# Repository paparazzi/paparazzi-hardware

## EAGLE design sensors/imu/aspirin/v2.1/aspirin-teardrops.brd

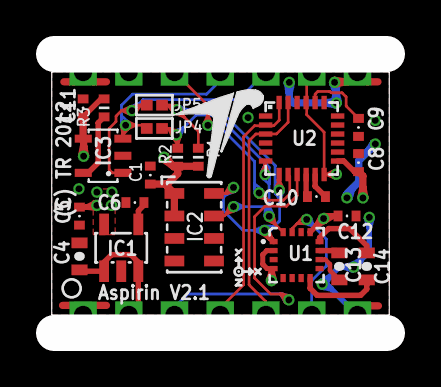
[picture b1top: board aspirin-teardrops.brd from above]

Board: 4 copper layers, 18.8 x 15.5 mm, 23 parts (0 on the bottom side), 20 nets.

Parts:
ASP1: ASPIRIN; ASPIRIN_CASTELLATED
C1, C8, C10, C11, C12: 100n; 0402-CAP
C4: 2.2uF/Low ESR; 0603-CAP
C5: 4.7uF/10V/Low ESR; 0402-CAP
C6: 10nF; 0402-CAP
C9: 2n2; 0402-CAP
C13: 4.7uF/10V/Low ESR; 0603-CAP
C14: 220n/Low ESR; 0603-CAP
IC1: LP2992; SOT23-5
IC2: MS5611; QFN-MS5611
IC3: >4KBIT SERIAL EEPROM HALF PROTECT; SOT23-5
JP4, JP5: 0/DNP; 0402-SQJMP
R1, R2, R3: 4k7; 0402-RES
U1: HMC5883; PLCC16-HMC5883
U2: MPU-6000; QFN24-NO-PAD
U$1: TR-LOGO

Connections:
+3V3: C1.P$1, C5.P$1, C8.P$1, C11.P$1, C12.P$1, IC1.5, IC2.1, IC2.2, IC3.4, R1.P$1, R2.P$1, R3.P$2, U1.2, U1.4, U1.13, U2.13
+6V5: ASP1.2, C4.P$1, IC1.1, IC1.3
ACC_CS: ASP1.12, U2.8
GND: ASP1.1, ASP1.7, ASP1.8, ASP1.14, C1.P$2, C4.P$2, C5.P$2, C6.P$1, C8.P$2, C9.P$2, C10.P$2, C11.P$2, C12.P$2, C13.P$2, IC1.2, IC2.3, IC2.4, IC2.5, IC3.2, U1.9, U1.11, U2.1, U2.11, U2.18
GYRO_INT: ASP1.9, U2.12
MAG_INT: ASP1.6, U1.15
MISO: ASP1.3, U2.9
MOSI: ASP1.4, U2.24
unnamed: C9.P$1, U2.20
unnamed: C10.P$1, U2.10
unnamed: C13.P$1, U1.10
unnamed: IC3.5, R3.P$1
unnamed: C6.P$2, IC1.4
unnamed: C14.P$2, U1.8
unnamed: C14.P$1, U1.12
SCK: ASP1.5, U2.23
SCL: IC2.8, JP5.P$2, R1.P$2, U1.1, U2.7
SDA: IC2.7, JP4.P$2, R2.P$2, U1.16, U2.6
XSCL: ASP1.10, IC3.1, JP5.P$1
XSDA: ASP1.11, IC3.3, JP4.P$1

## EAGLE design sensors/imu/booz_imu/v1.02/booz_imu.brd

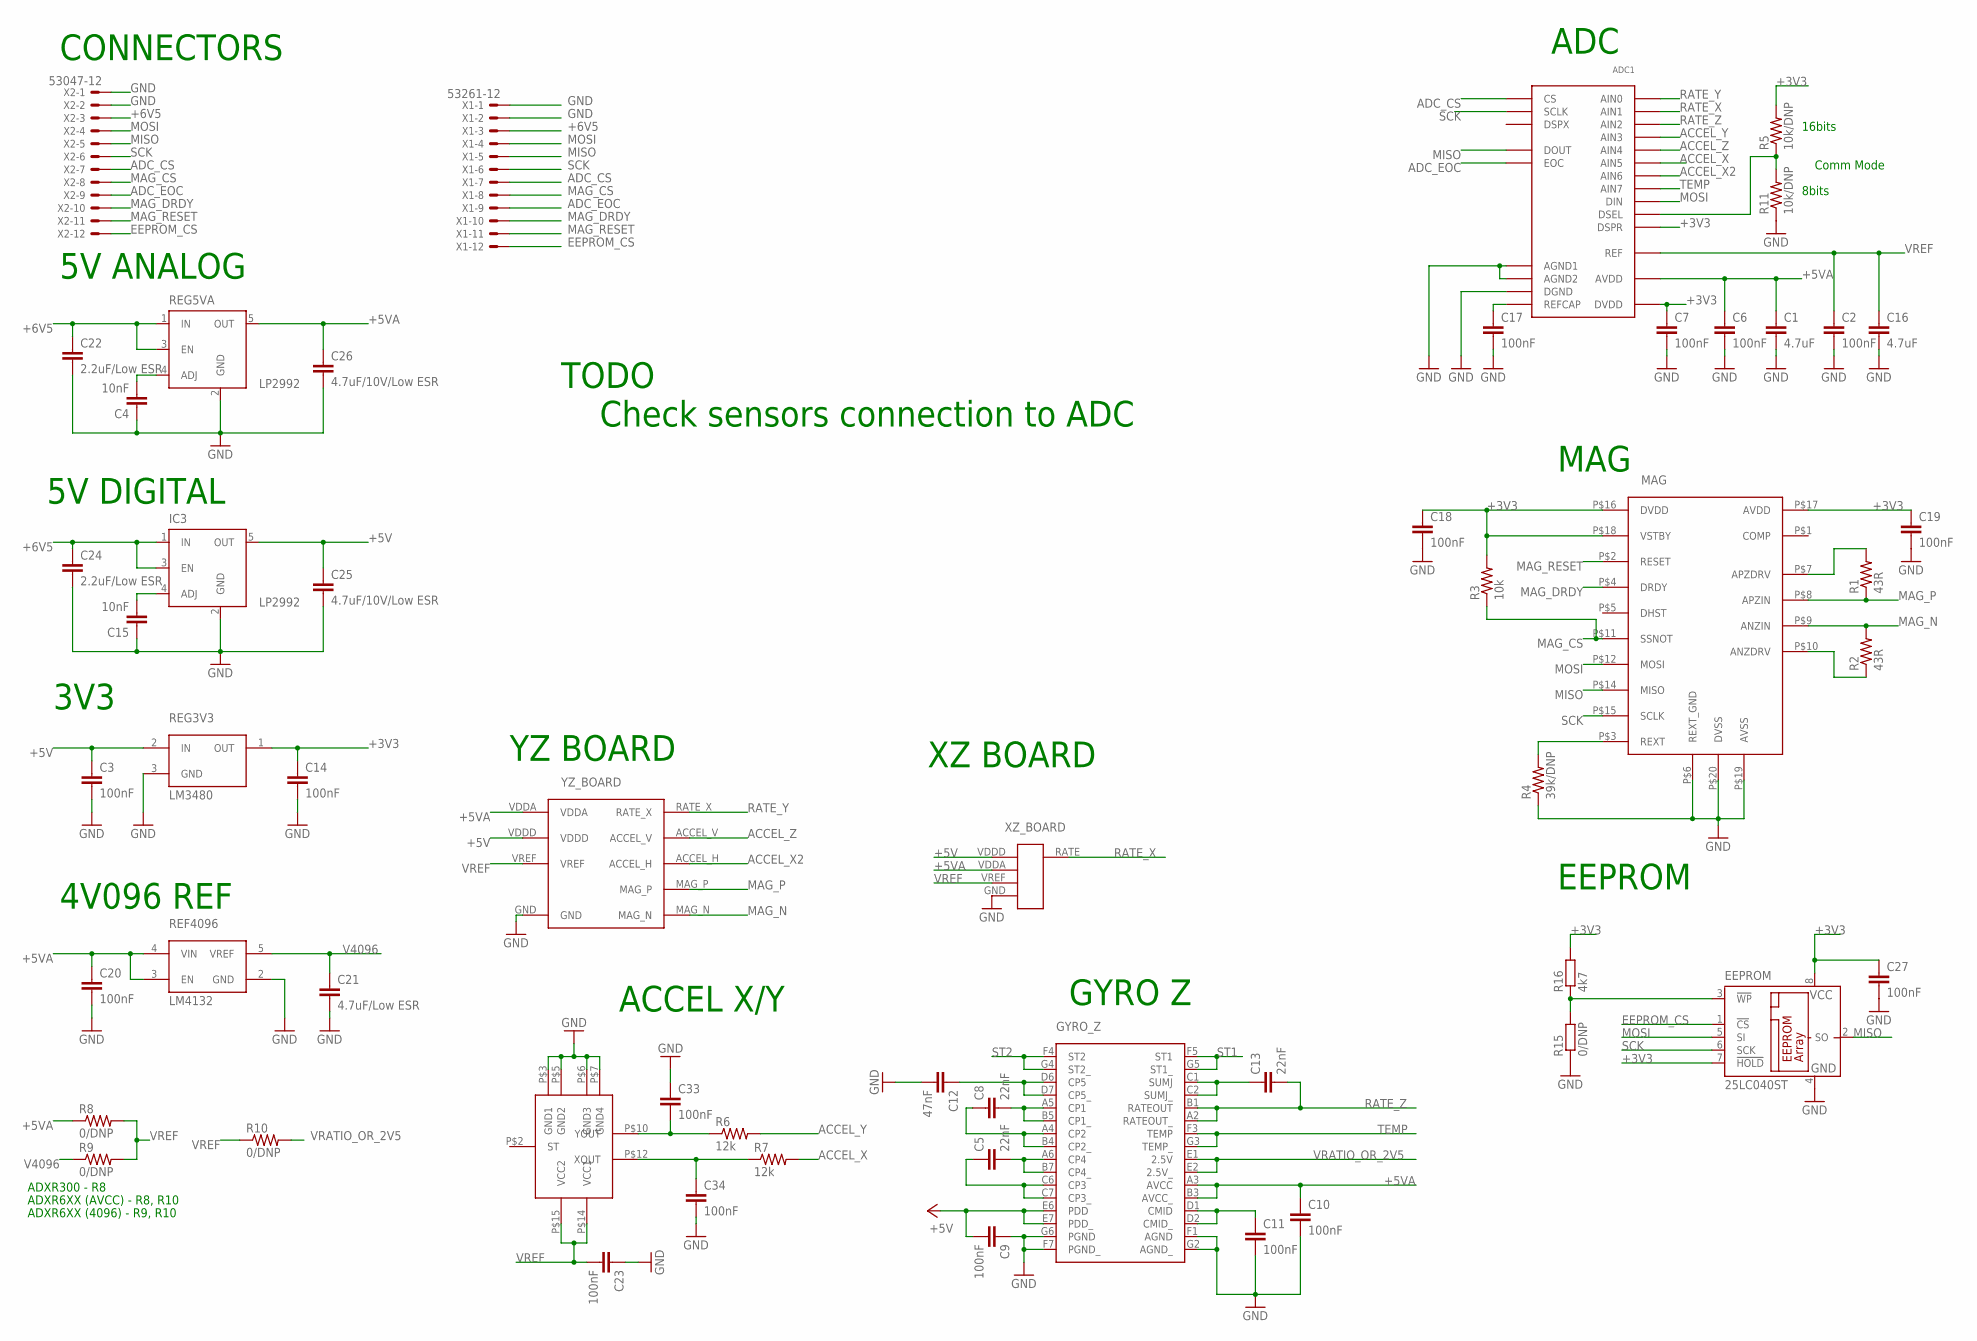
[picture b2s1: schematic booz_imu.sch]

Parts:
ADC1: MAX1168; QSOP24
C1, C16: 4.7uF; C0805
C2, C3, C6, C7, C9, C10, C11, C14, C17, C18, C19, C20, C23, C33, C34: 100nF; C0603K
C4, C15: 10nF; C0603K
C5, C8, C13: 22nF; C0603K
C12: 47nF; C0603K
C21: 4.7uF/Low ESR; C0805K
C22, C24: 2.2uF/Low ESR; C0603K
C25, C26: 4.7uF/10V/Low ESR; C0805K
C27: 100nF; C0603
EEPROM: 25LC040ST; TSSOP8
GYRO_Z: ADXR; BC-32
IC3: LP2992; SOT23-5
MAG: MS2100; QFN20
R1, R2: 43R; R0603
R3: 10k; R0603
R4: 39k/DNP; R0603
R5, R11: 10k/DNP; R0603
R6, R7: 12k; R0603
R8, R9, R10, R15: 0/DNP; R0603
R16: 4k7; R0603
REF4096: LM4132; SOT23-5L
REG3V3: LM3480; SOT23
REG5VA: LP2992; SOT23-5
U$2: ADXL320; LSCFP
X1: 53261-12
X2: 53047-12
XZ_BOARD: IMU_XZ_2; IMU_XZ
YZ_BOARD: IMU_YZ_MAG_2; IMU_YZ_MAG

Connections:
+3V3: ADC1.P$1 (DSPR), ADC1.P$22 (DVDD), C7.1, C14.1, C18.1, C19.1, C27.1, EEPROM.7 (!HOLD), EEPROM.8 (VCC), MAG.P$16 (DVDD), MAG.P$17 (AVDD), MAG.P$18 (VSTBY), R3.2, R5.2, R16.2, REG3V3.1 (OUT)
+5V: C3.1, C9.2, C25.1, GYRO_Z.E6 (PDD), GYRO_Z.E7 (PDD_), IC3.5 (OUT), REG3V3.2 (IN), XZ_BOARD.VDDD, YZ_BOARD.VDDD
+5VA: ADC1.P$19 (AVDD), C1.1, C6.1, C10.1, C20.1, C26.1, GYRO_Z.A3 (AVCC), GYRO_Z.B3 (AVCC_), R8.1, REF4096.3 (EN), REF4096.4 (VIN), REG5VA.5 (OUT), XZ_BOARD.VDDA, YZ_BOARD.VDDA
+6V5: C22.1, C24.1, IC3.1 (IN), IC3.3 (EN), REG5VA.1 (IN), REG5VA.3 (EN), X1.3, X2.3
ACCEL_X: ADC1.P$12 (AIN5), R7.2
ACCEL_X2: ADC1.P$13 (AIN6), YZ_BOARD.ACCEL_H
ACCEL_Y: ADC1.P$10 (AIN3), R6.2
ACCEL_Z: ADC1.P$11 (AIN4), YZ_BOARD.ACCEL_V
ADC_CS: ADC1.P$20 (CS), X1.7, X2.7
ADC_EOC: ADC1.P$6 (EOC), X1.9, X2.9
EEPROM_CS: EEPROM.1 (!CS), X1.12, X2.12
GND: ADC1.P$17 (AGND1), ADC1.P$18 (AGND2), ADC1.P$21 (DGND), C1.2, C2.2, C3.2, C4.1, C6.2, C7.2, C9.1, C10.2, C11.2, C12.2, C14.2, C15.1, C16.2, C17.2, C18.2, C19.2, C20.2, C21.2, C22.2, C23.1, C24.2, C25.2, C26.2, C27.2, C33.1, C34.2, EEPROM.4 (GND), GYRO_Z.F1 (AGND), GYRO_Z.F7 (PGND_), GYRO_Z.G2 (AGND_), GYRO_Z.G6 (PGND), IC3.2 (GND), MAG.P$6 (REXT_GND), MAG.P$19 (AVSS), MAG.P$20 (DVSS), R4.1, R11.1, R15.1, REF4096.2 (GND), REG3V3.3 (GND), REG5VA.2 (GND), U$2.P$3 (GND1), U$2.P$5 (GND2), U$2.P$6 (GND3), U$2.P$7 (GND4), X1.1, X1.2, X2.1, X2.2, XZ_BOARD.GND, YZ_BOARD.GND
MAG_CS: MAG.P$11 (SSNOT), R3.1, X1.8, X2.8
MAG_DRDY: MAG.P$4 (DRDY), X1.10, X2.10
MAG_N: MAG.P$9 (ANZIN), R2.2, YZ_BOARD.MAG_N
MAG_P: MAG.P$8 (APZIN), R1.1, YZ_BOARD.MAG_P
MAG_RESET: MAG.P$2 (RESET), X1.11, X2.11
MISO: ADC1.P$3 (DOUT), EEPROM.2 (SO), MAG.P$14 (MISO), X1.5, X2.5
MOSI: ADC1.P$5 (DIN), EEPROM.5 (SI), MAG.P$12 (MOSI), X1.4, X2.4
unnamed: ADC1.P$2 (DSEL), R5.1, R11.2
unnamed: ADC1.P$16 (REFCAP), C17.1
unnamed: C5.2, GYRO_Z.A6 (CP4), GYRO_Z.B7 (CP4_)
unnamed: C5.1, GYRO_Z.C6 (CP3), GYRO_Z.C7 (CP3_)
unnamed: C8.2, GYRO_Z.A5 (CP1), GYRO_Z.B5 (CP1_)
unnamed: C8.1, GYRO_Z.A4 (CP2), GYRO_Z.B4 (CP2_)
unnamed: C13.1, GYRO_Z.C1 (SUMJ), GYRO_Z.C2 (SUMJ_)
unnamed: C12.1, GYRO_Z.D6 (CP5), GYRO_Z.D7 (CP5_)
unnamed: C11.1, GYRO_Z.D1 (CMID), GYRO_Z.D2 (CMID_)
unnamed: MAG.P$10 (ANZDRV), R2.1
unnamed: MAG.P$7 (APZDRV), R1.2
unnamed: MAG.P$3 (REXT), R4.2
unnamed: C15.2, IC3.4 (ADJ)
unnamed: C33.2, R6.1, U$2.P$10 (YOUT)
unnamed: C4.2, REG5VA.4 (ADJ)
unnamed: C34.1, R7.1, U$2.P$12 (XOUT)
unnamed: EEPROM.3 (!WP), R15.2, R16.1
RATE_X: ADC1.P$8 (AIN1), XZ_BOARD.RATE
RATE_Y: ADC1.P$7 (AIN0), YZ_BOARD.RATE_X
RATE_Z: ADC1.P$9 (AIN2), C13.2, GYRO_Z.A2 (RATEOUT_), GYRO_Z.B1 (RATEOUT)
SCK: ADC1.P$4 (SCLK), EEPROM.6 (SCK), MAG.P$15 (SCLK), X1.6, X2.6
ST1: GYRO_Z.F5 (ST1), GYRO_Z.G5 (ST1_)
ST2: GYRO_Z.F4 (ST2), GYRO_Z.G4 (ST2_)
TEMP: ADC1.P$14 (AIN7), GYRO_Z.F3 (TEMP), GYRO_Z.G3 (TEMP_)
V4096: C21.1, R9.1, REF4096.5 (VREF)
VRATIO_OR_2V5: GYRO_Z.E1 (2.5V), GYRO_Z.E2 (2.5V_), R10.2
VREF: ADC1.P$15 (REF), C2.1, C16.1, C23.2, R8.2, R9.2, R10.1, U$2.P$14 (VCC1), U$2.P$15 (VCC2), XZ_BOARD.VREF, YZ_BOARD.VREF

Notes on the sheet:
5V ANALOG
5V DIGITAL
Comm Mode
ADXR300 - R8
ADXR6XX (AVCC) - R8, R10
ADXR6XX (4096) - R9, R10
3V3
4V096 REF
CONNECTORS
ADC
GYRO Z
ACCEL X/Y
XZ BOARD
YZ BOARD
MAG
EEPROM
TODO
Check sensors connection to ADC
16bits
8bits

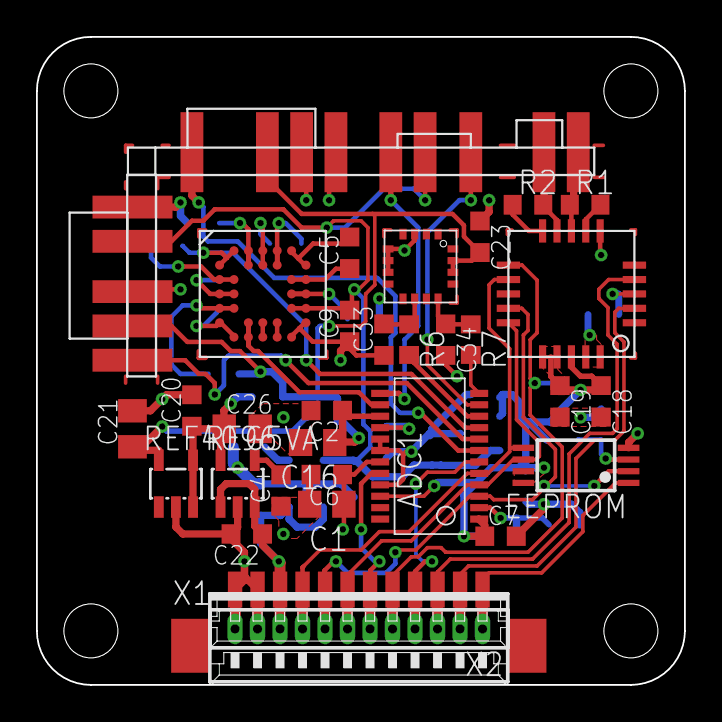
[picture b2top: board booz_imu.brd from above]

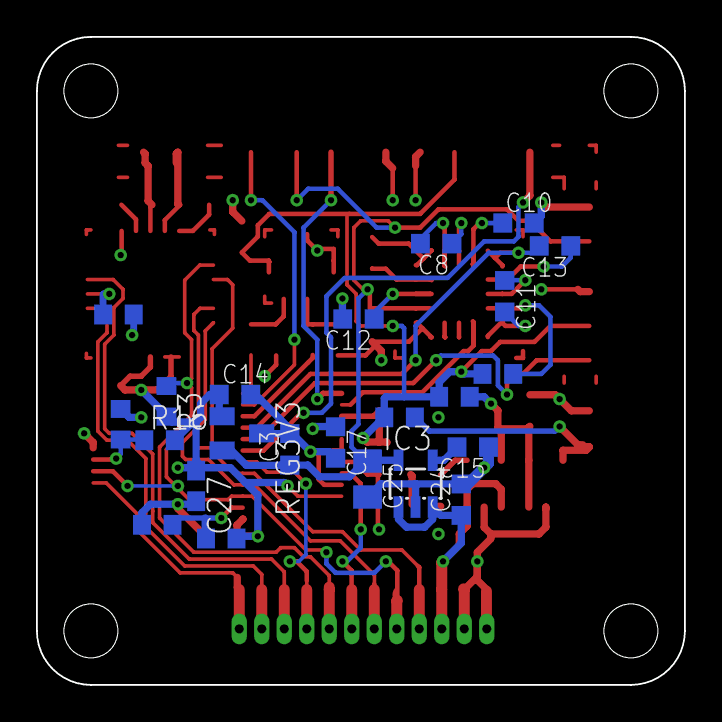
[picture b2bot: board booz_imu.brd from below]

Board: 4 copper layers, 36.0 x 36.0 mm, 55 parts (23 on the bottom side), 46 nets.

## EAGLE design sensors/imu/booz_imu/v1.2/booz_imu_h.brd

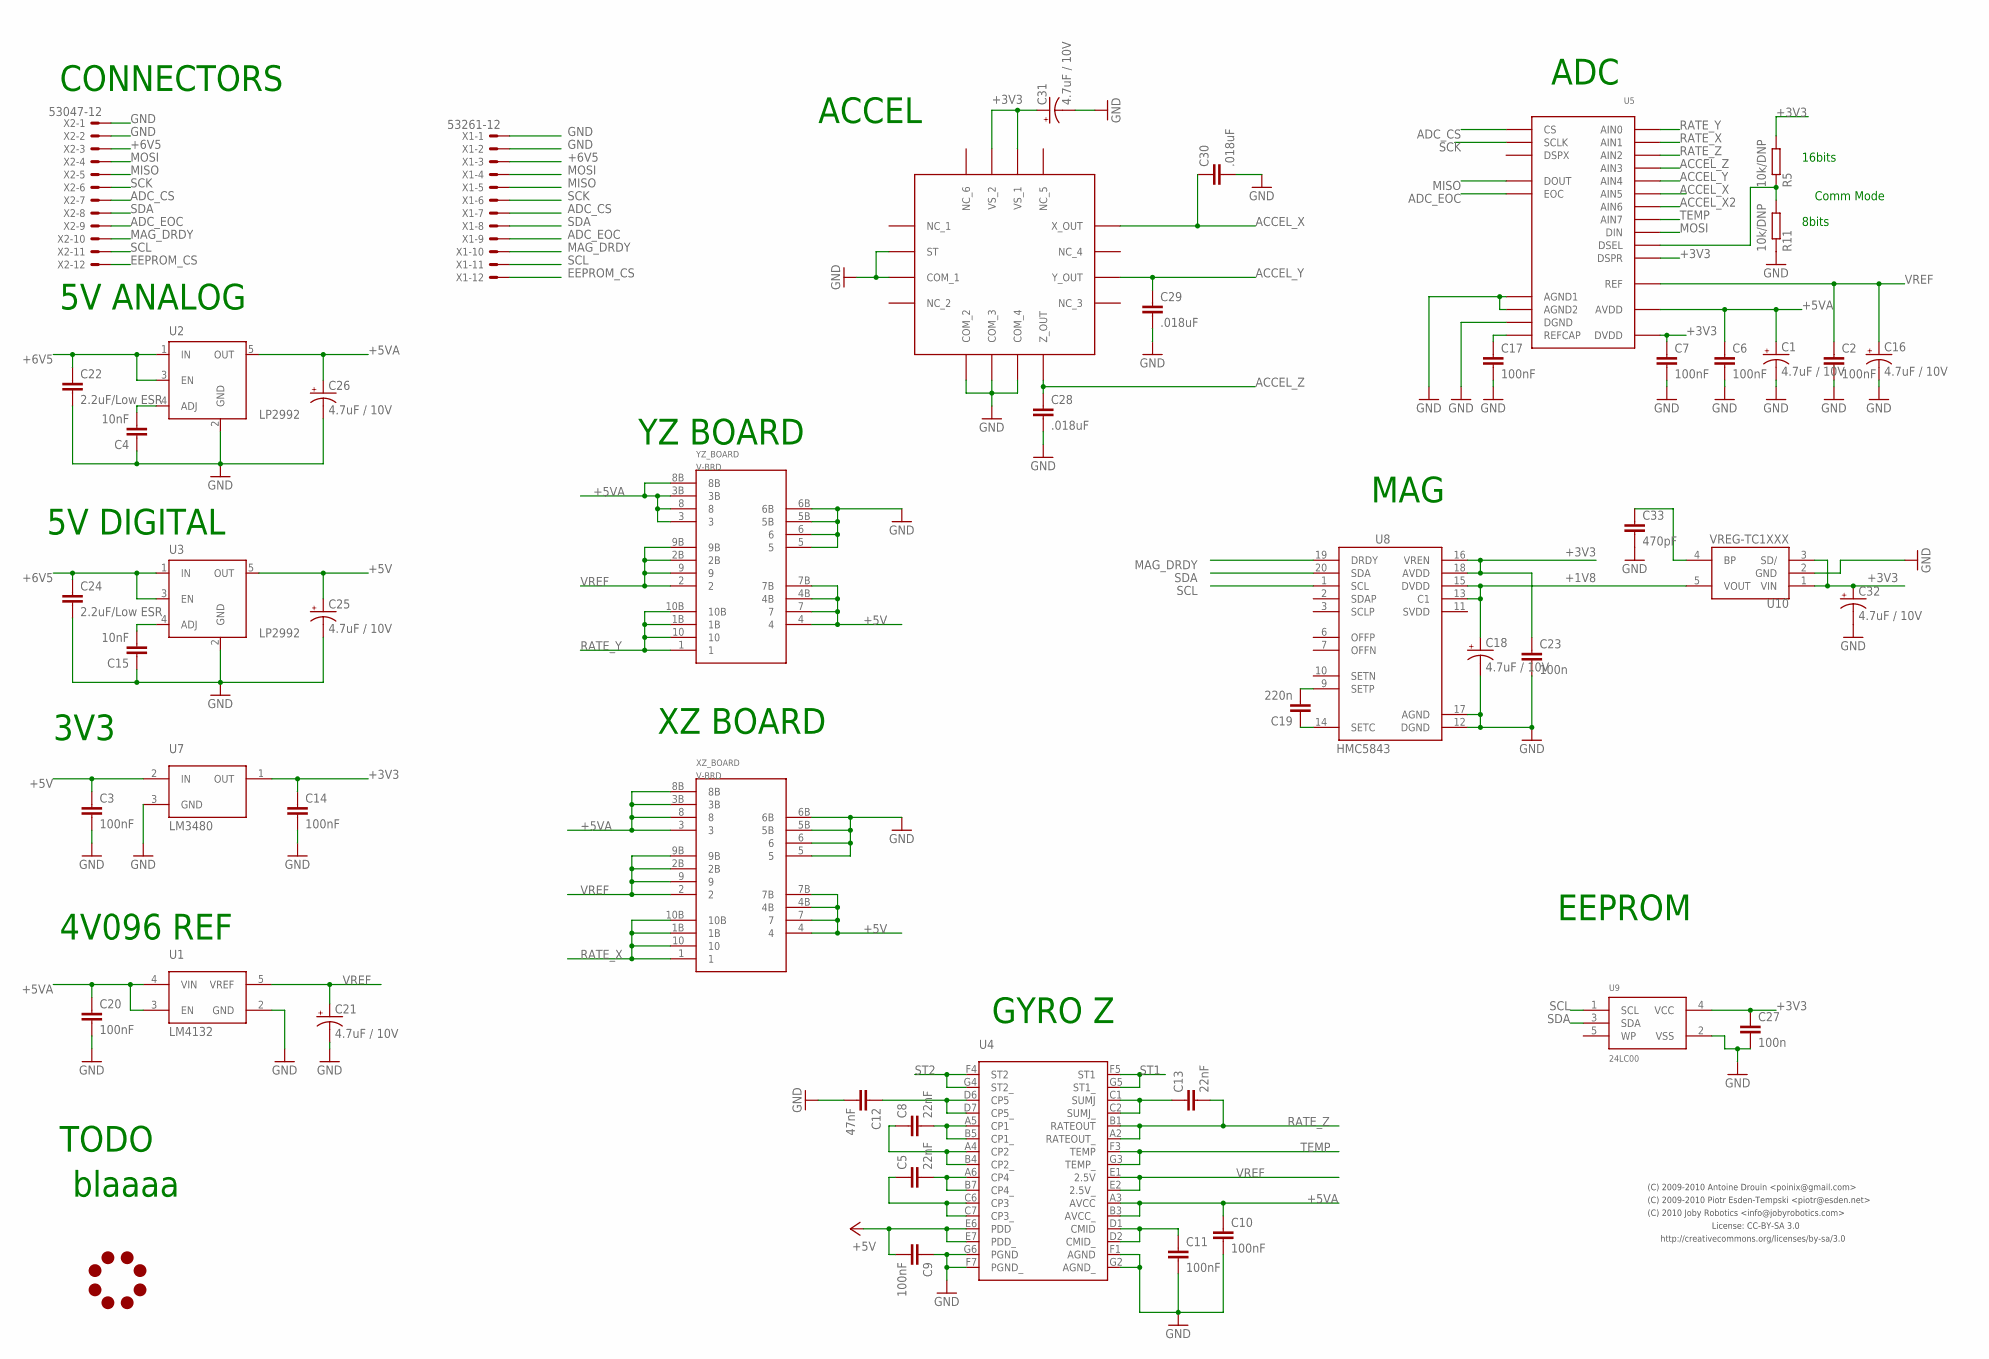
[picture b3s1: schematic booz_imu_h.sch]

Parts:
C1, C16, C18, C21, C25, C26, C31, C32: 4.7uF / 10V; CAP_0805TANT_F95
C2, C3, C6, C7, C9, C10, C11, C14, C17, C20: 100nF; 0603-CAP
C4, C15: 10nF; 0603-CAP
C5, C8, C13: 22nF; 0603-CAP
C12: 47nF; 0603-CAP
C19: 220n; 0603-CAP
C22, C24: 2.2uF/Low ESR; 0603-CAP
C23, C27: 100n; 0603-CAP
C28, C29, C30: .018uF; 0603-CAP
C33: 470pF; 0603-CAP
JL1: JOBY_LOGO-6MIL; JOBY_LOGO_6MIL
R5, R11: 10k/DNP; 0603-RES
U1: LM4132; SOT23-5L
U2, U3: LP2992; SOT23-5
U4: ADXR; BC-32
U5: MAX1168; QSOP24
U6: ADXL335; LFCSP_LQ16
U7: LM3480; SOT23
U8: HMC5843; LPCC20-HMC5843
U9: 24LC00; SOT23-5
U10: VREG-TC1XXX; SOT23-5
X1: 53261-12
X2: 53047-12
XZ_BOARD: V-BRD
YZ_BOARD: V-BRD

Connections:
+1V8: C18.P$1 (+), U8.13 (C1), U8.15 (DVDD), U10.5 (VOUT)
+3V3: C7.P$1 (1), C14.P$1 (1), C23.P$1 (1), C27.P$1 (1), C31.P$1 (+), C32.P$1 (+), R5.P$2 (2), U5.P$1 (DSPR), U5.P$22 (DVDD), U6.P$14 (VS_1), U6.P$15 (VS_2), U7.1 (OUT), U8.16 (VREN), U8.18 (AVDD), U9.4 (VCC), U10.1 (VIN), U10.3 (SD/)
+5V: C3.P$1 (1), C9.P$2 (2), C25.P$1 (+), U3.5 (OUT), U4.E6 (PDD), U4.E7 (PDD_), U7.2 (IN), XZ_BOARD.4, XZ_BOARD.4B, XZ_BOARD.7, XZ_BOARD.7B, YZ_BOARD.4, YZ_BOARD.4B, YZ_BOARD.7, YZ_BOARD.7B
+5VA: C1.P$1 (+), C6.P$1 (1), C10.P$1 (1), C20.P$1 (1), C26.P$1 (+), U1.3 (EN), U1.4 (VIN), U2.5 (OUT), U4.A3 (AVCC), U4.B3 (AVCC_), U5.P$19 (AVDD), XZ_BOARD.3, XZ_BOARD.3B, XZ_BOARD.8, XZ_BOARD.8B, YZ_BOARD.3, YZ_BOARD.3B, YZ_BOARD.8, YZ_BOARD.8B
+6V5: C22.P$1 (1), C24.P$1 (1), U2.1 (IN), U2.3 (EN), U3.1 (IN), U3.3 (EN), X1.3, X2.3
ACCEL_X: C30.P$1 (1), U5.P$12 (AIN5), U6.P$12 (X_OUT)
ACCEL_X2: U5.P$13 (AIN6)
ACCEL_Y: C29.P$1 (1), U5.P$11 (AIN4), U6.P$10 (Y_OUT)
ACCEL_Z: C28.P$1 (1), U5.P$10 (AIN3), U6.P$8 (Z_OUT)
ADC_CS: U5.P$20 (CS), X1.7, X2.7
ADC_EOC: U5.P$6 (EOC), X1.9, X2.9
EEPROM_CS: X1.12, X2.12
GND: C1.P$2 (-), C2.P$2 (2), C3.P$2 (2), C4.P$1 (1), C6.P$2 (2), C7.P$2 (2), C9.P$1 (1), C10.P$2 (2), C11.P$2 (2), C12.P$2 (2), C14.P$2 (2), C15.P$1 (1), C16.P$2 (-), C17.P$2 (2), C18.P$2 (-), C20.P$2 (2), C21.P$2 (-), C22.P$2 (2), C23.P$2 (2), C24.P$2 (2), C25.P$2 (-), C26.P$2 (-), C27.P$2 (2), C28.P$2 (2), C29.P$2 (2), C30.P$2 (2), C31.P$2 (-), C32.P$2 (-), C33.P$2 (2), R11.P$1 (1), U1.2 (GND), U2.2 (GND), U3.2 (GND), U4.F1 (AGND), U4.F7 (PGND_), U4.G2 (AGND_), U4.G6 (PGND), U5.P$17 (AGND1), U5.P$18 (AGND2), U5.P$21 (DGND), U6.P$2 (ST), U6.P$3 (COM_1), U6.P$5 (COM_2), U6.P$6 (COM_3), U6.P$7 (COM_4), U7.3 (GND), U8.12 (DGND), U8.17 (AGND), U9.2 (VSS), U10.2 (GND), X1.1, X1.2, X2.1, X2.2, XZ_BOARD.5, XZ_BOARD.5B, XZ_BOARD.6, XZ_BOARD.6B, YZ_BOARD.5, YZ_BOARD.5B, YZ_BOARD.6, YZ_BOARD.6B
MAG_DRDY: U8.19 (DRDY), X1.10, X2.10
MISO: U5.P$3 (DOUT), X1.5, X2.5
MOSI: U5.P$5 (DIN), X1.4, X2.4
unnamed: R5.P$1 (1), R11.P$2 (2), U5.P$2 (DSEL)
unnamed: C17.P$1 (1), U5.P$16 (REFCAP)
unnamed: C33.P$1 (1), U10.4 (BP)
unnamed: C5.P$2 (2), U4.A6 (CP4), U4.B7 (CP4_)
unnamed: C5.P$1 (1), U4.C6 (CP3), U4.C7 (CP3_)
unnamed: C8.P$2 (2), U4.A5 (CP1), U4.B5 (CP1_)
unnamed: C8.P$1 (1), U4.A4 (CP2), U4.B4 (CP2_)
unnamed: C13.P$1 (1), U4.C1 (SUMJ), U4.C2 (SUMJ_)
unnamed: C12.P$1 (1), U4.D6 (CP5), U4.D7 (CP5_)
unnamed: C11.P$1 (1), U4.D1 (CMID), U4.D2 (CMID_)
unnamed: C19.P$2 (2), U8.9 (SETP)
unnamed: C15.P$2 (2), U3.4 (ADJ)
unnamed: C4.P$2 (2), U2.4 (ADJ)
unnamed: C19.P$1 (1), U8.14 (SETC)
RATE_X: U5.P$8 (AIN1), XZ_BOARD.1, XZ_BOARD.1B, XZ_BOARD.10, XZ_BOARD.10B
RATE_Y: U5.P$7 (AIN0), YZ_BOARD.1, YZ_BOARD.1B, YZ_BOARD.10, YZ_BOARD.10B
RATE_Z: C13.P$2 (2), U4.A2 (RATEOUT_), U4.B1 (RATEOUT), U5.P$9 (AIN2)
SCK: U5.P$4 (SCLK), X1.6, X2.6
SCL: U8.1 (SCL), U9.1 (SCL), X1.11, X2.11
SDA: U8.20 (SDA), U9.3 (SDA), X1.8, X2.8
ST1: U4.F5 (ST1), U4.G5 (ST1_)
ST2: U4.F4 (ST2), U4.G4 (ST2_)
TEMP: U4.F3 (TEMP), U4.G3 (TEMP_), U5.P$14 (AIN7)
VREF: C2.P$1 (1), C16.P$1 (+), C21.P$1 (+), U1.5 (VREF), U4.E1 (2.5V), U4.E2 (2.5V_), U5.P$15 (REF), XZ_BOARD.2, XZ_BOARD.2B, XZ_BOARD.9, XZ_BOARD.9B, YZ_BOARD.2, YZ_BOARD.2B, YZ_BOARD.9, YZ_BOARD.9B

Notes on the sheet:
5V ANALOG
5V DIGITAL
Comm Mode
3V3
4V096 REF
CONNECTORS
ADC
GYRO Z
ACCEL
XZ BOARD
YZ BOARD
EEPROM
TODO
blaaaa
16bits
8bits
MAG
License: CC-BY-SA 3.0
http://creativecommons.org/licenses/by-sa/3.0
(C) 2009-2010 Piotr Esden-Tempski <piotr@esden.net>
(C) 2009-2010 Antoine Drouin <poinix@gmail.com>
(C) 2010 Joby Robotics <info@jobyrobotics.com>

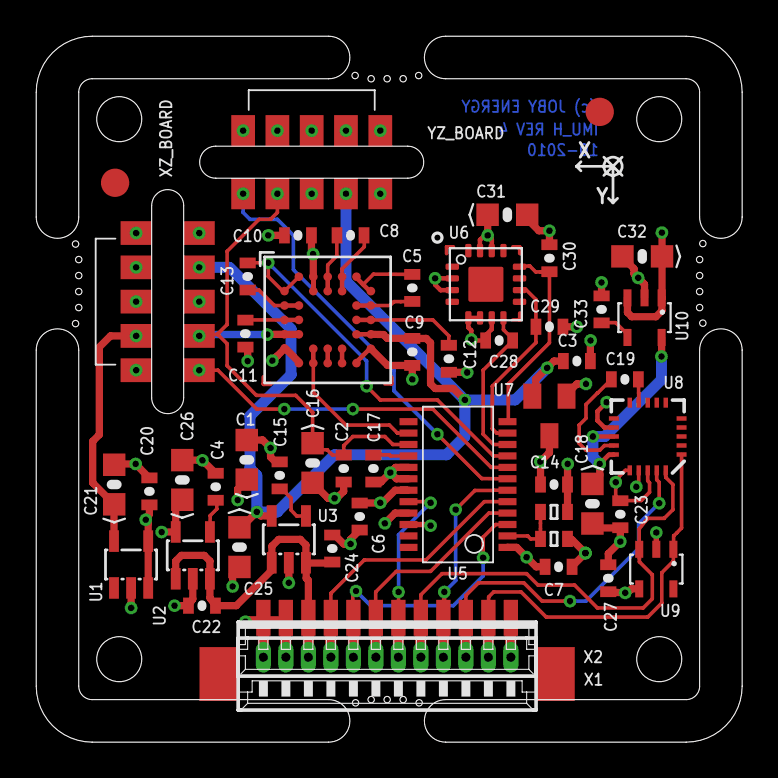
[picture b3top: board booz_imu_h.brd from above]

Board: 4 copper layers, 39.2 x 39.2 mm, 50 parts (1 on the bottom side), 39 nets.

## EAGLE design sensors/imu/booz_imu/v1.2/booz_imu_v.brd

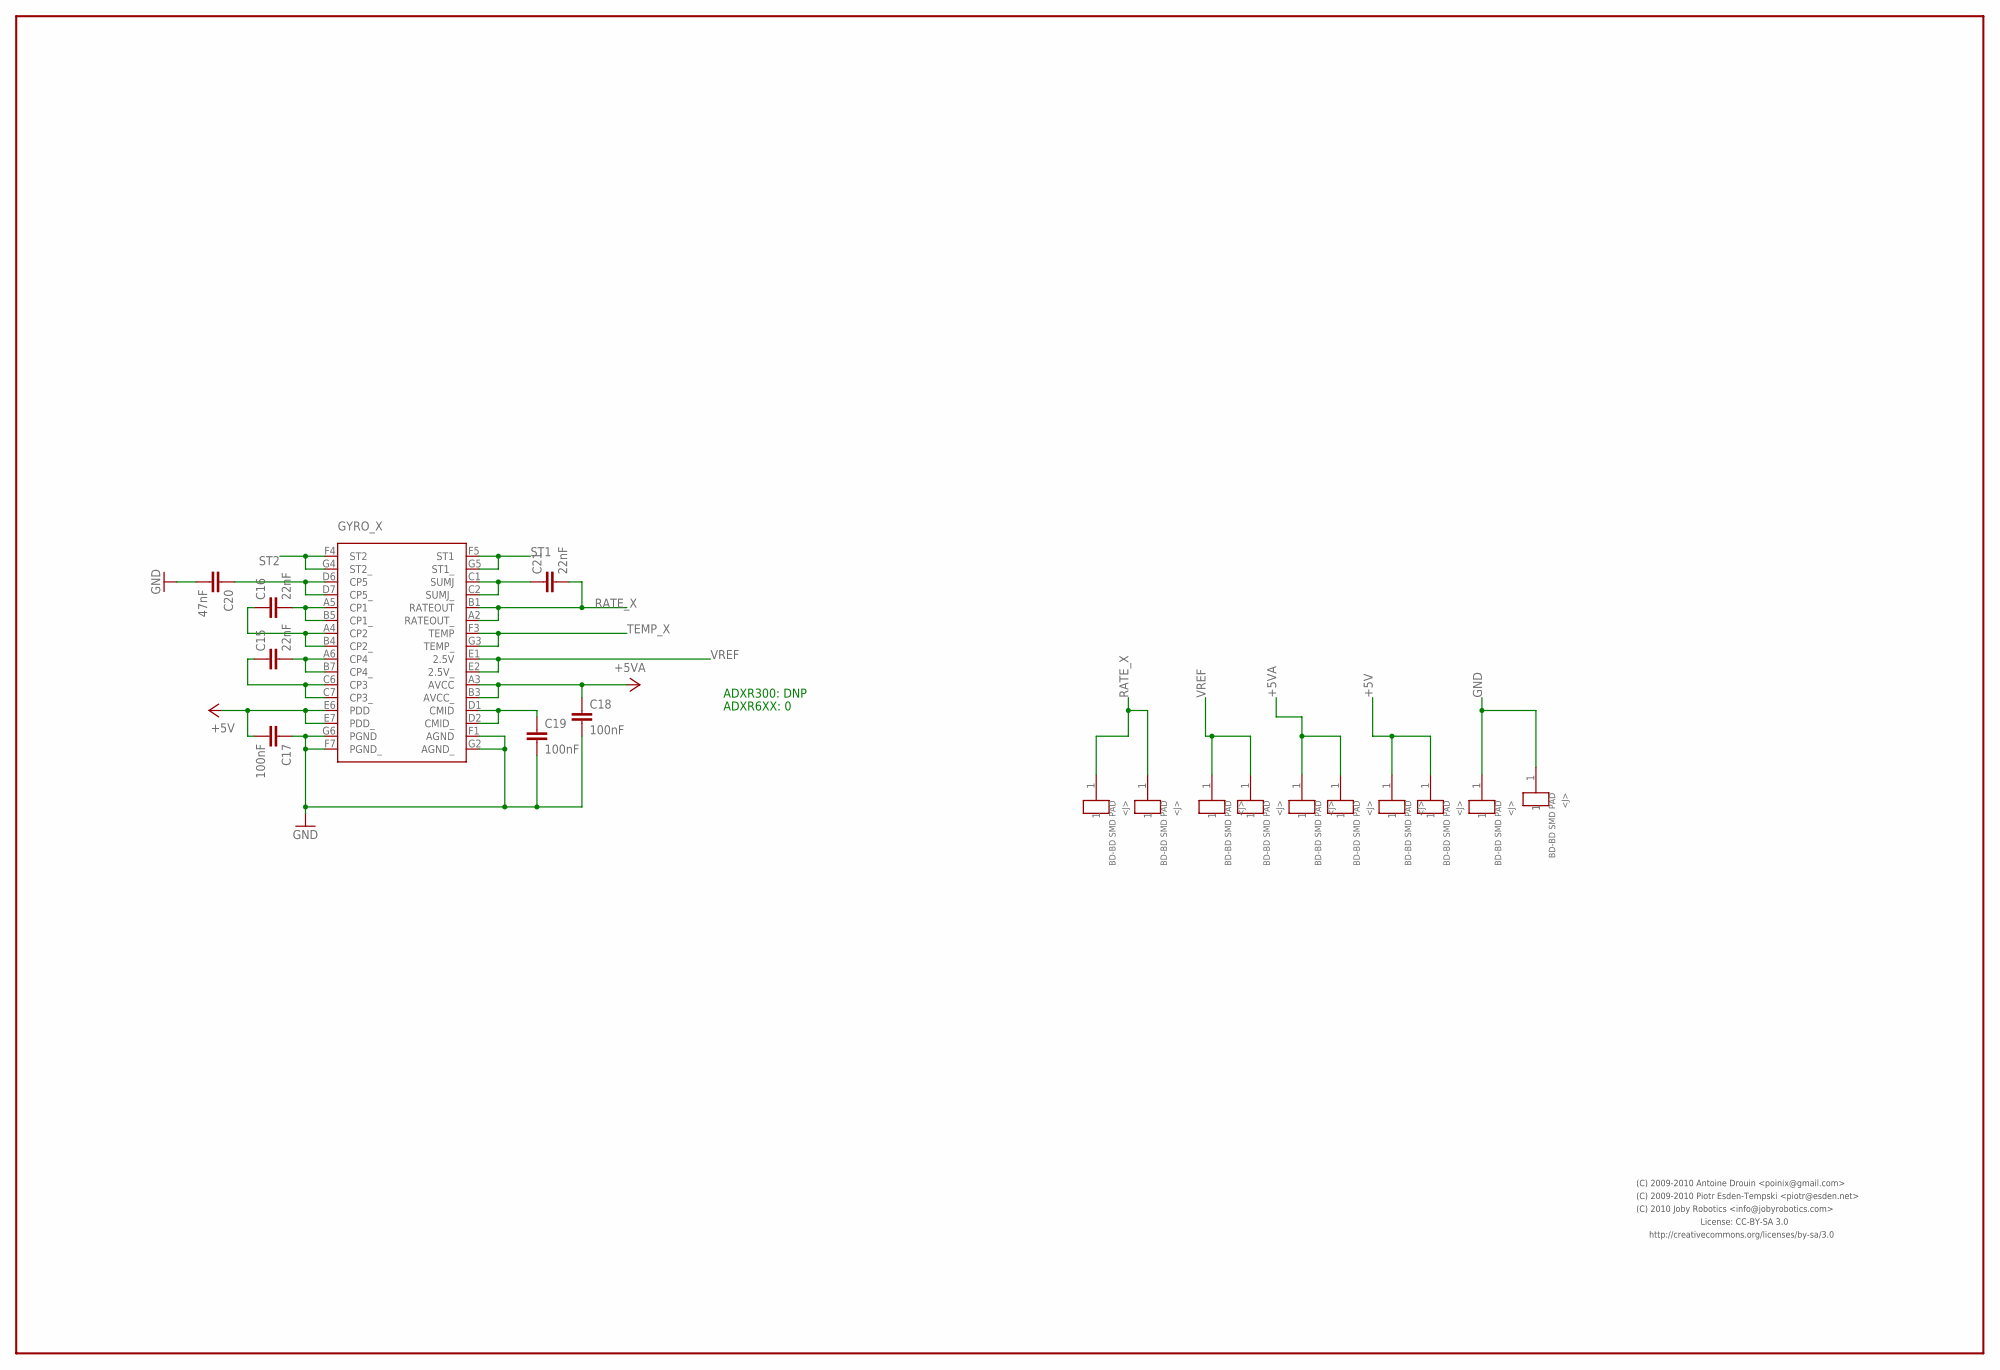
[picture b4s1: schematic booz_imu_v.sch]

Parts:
C15, C16, C21: 22nF; 0603-CAP
C17, C18, C19: 100nF; 0603-CAP
C20: 47nF; 0603-CAP
GYRO_X: ADXR; BC-32
J1, J2, J3, J4, J5, J6, J7, J8, J9, J10: SOLDERPAD25X160

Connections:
+5V: C17.P$2 (2), GYRO_X.E6 (PDD), GYRO_X.E7 (PDD_), J8.1, J9.1
+5VA: C18.P$1 (1), GYRO_X.A3 (AVCC), GYRO_X.B3 (AVCC_), J6.1, J7.1
GND: C17.P$1 (1), C18.P$2 (2), C19.P$2 (2), C20.P$2 (2), GYRO_X.F1 (AGND), GYRO_X.F7 (PGND_), GYRO_X.G2 (AGND_), GYRO_X.G6 (PGND), J2.1, J10.1
unnamed: C21.P$1 (1), GYRO_X.C1 (SUMJ), GYRO_X.C2 (SUMJ_)
unnamed: C15.P$1 (1), GYRO_X.C6 (CP3), GYRO_X.C7 (CP3_)
unnamed: C20.P$1 (1), GYRO_X.D6 (CP5), GYRO_X.D7 (CP5_)
unnamed: C16.P$2 (2), GYRO_X.A5 (CP1), GYRO_X.B5 (CP1_)
unnamed: C16.P$1 (1), GYRO_X.A4 (CP2), GYRO_X.B4 (CP2_)
unnamed: C15.P$2 (2), GYRO_X.A6 (CP4), GYRO_X.B7 (CP4_)
unnamed: C19.P$1 (1), GYRO_X.D1 (CMID), GYRO_X.D2 (CMID_)
RATE_X: C21.P$2 (2), GYRO_X.A2 (RATEOUT_), GYRO_X.B1 (RATEOUT), J1.1, J3.1
ST1: GYRO_X.F5 (ST1), GYRO_X.G5 (ST1_)
ST2: GYRO_X.F4 (ST2), GYRO_X.G4 (ST2_)
TEMP_X: GYRO_X.F3 (TEMP), GYRO_X.G3 (TEMP_)
VREF: GYRO_X.E1 (2.5V), GYRO_X.E2 (2.5V_), J4.1, J5.1

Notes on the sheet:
ADXR300: DNP
ADXR6XX: 0
License: CC-BY-SA 3.0
http://creativecommons.org/licenses/by-sa/3.0
(C) 2009-2010 Piotr Esden-Tempski <piotr@esden.net>
(C) 2009-2010 Antoine Drouin <poinix@gmail.com>
(C) 2010 Joby Robotics <info@jobyrobotics.com>

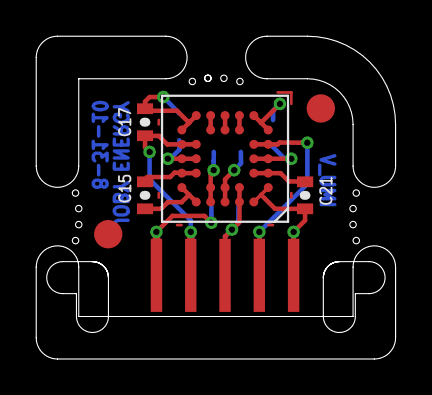
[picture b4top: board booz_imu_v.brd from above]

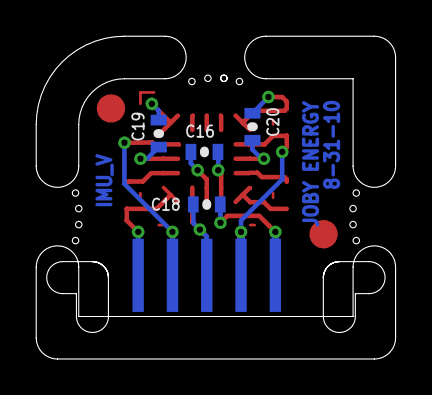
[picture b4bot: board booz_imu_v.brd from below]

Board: 4 copper layers, 20.0 x 17.9 mm, 18 parts (9 on the bottom side), 15 nets.

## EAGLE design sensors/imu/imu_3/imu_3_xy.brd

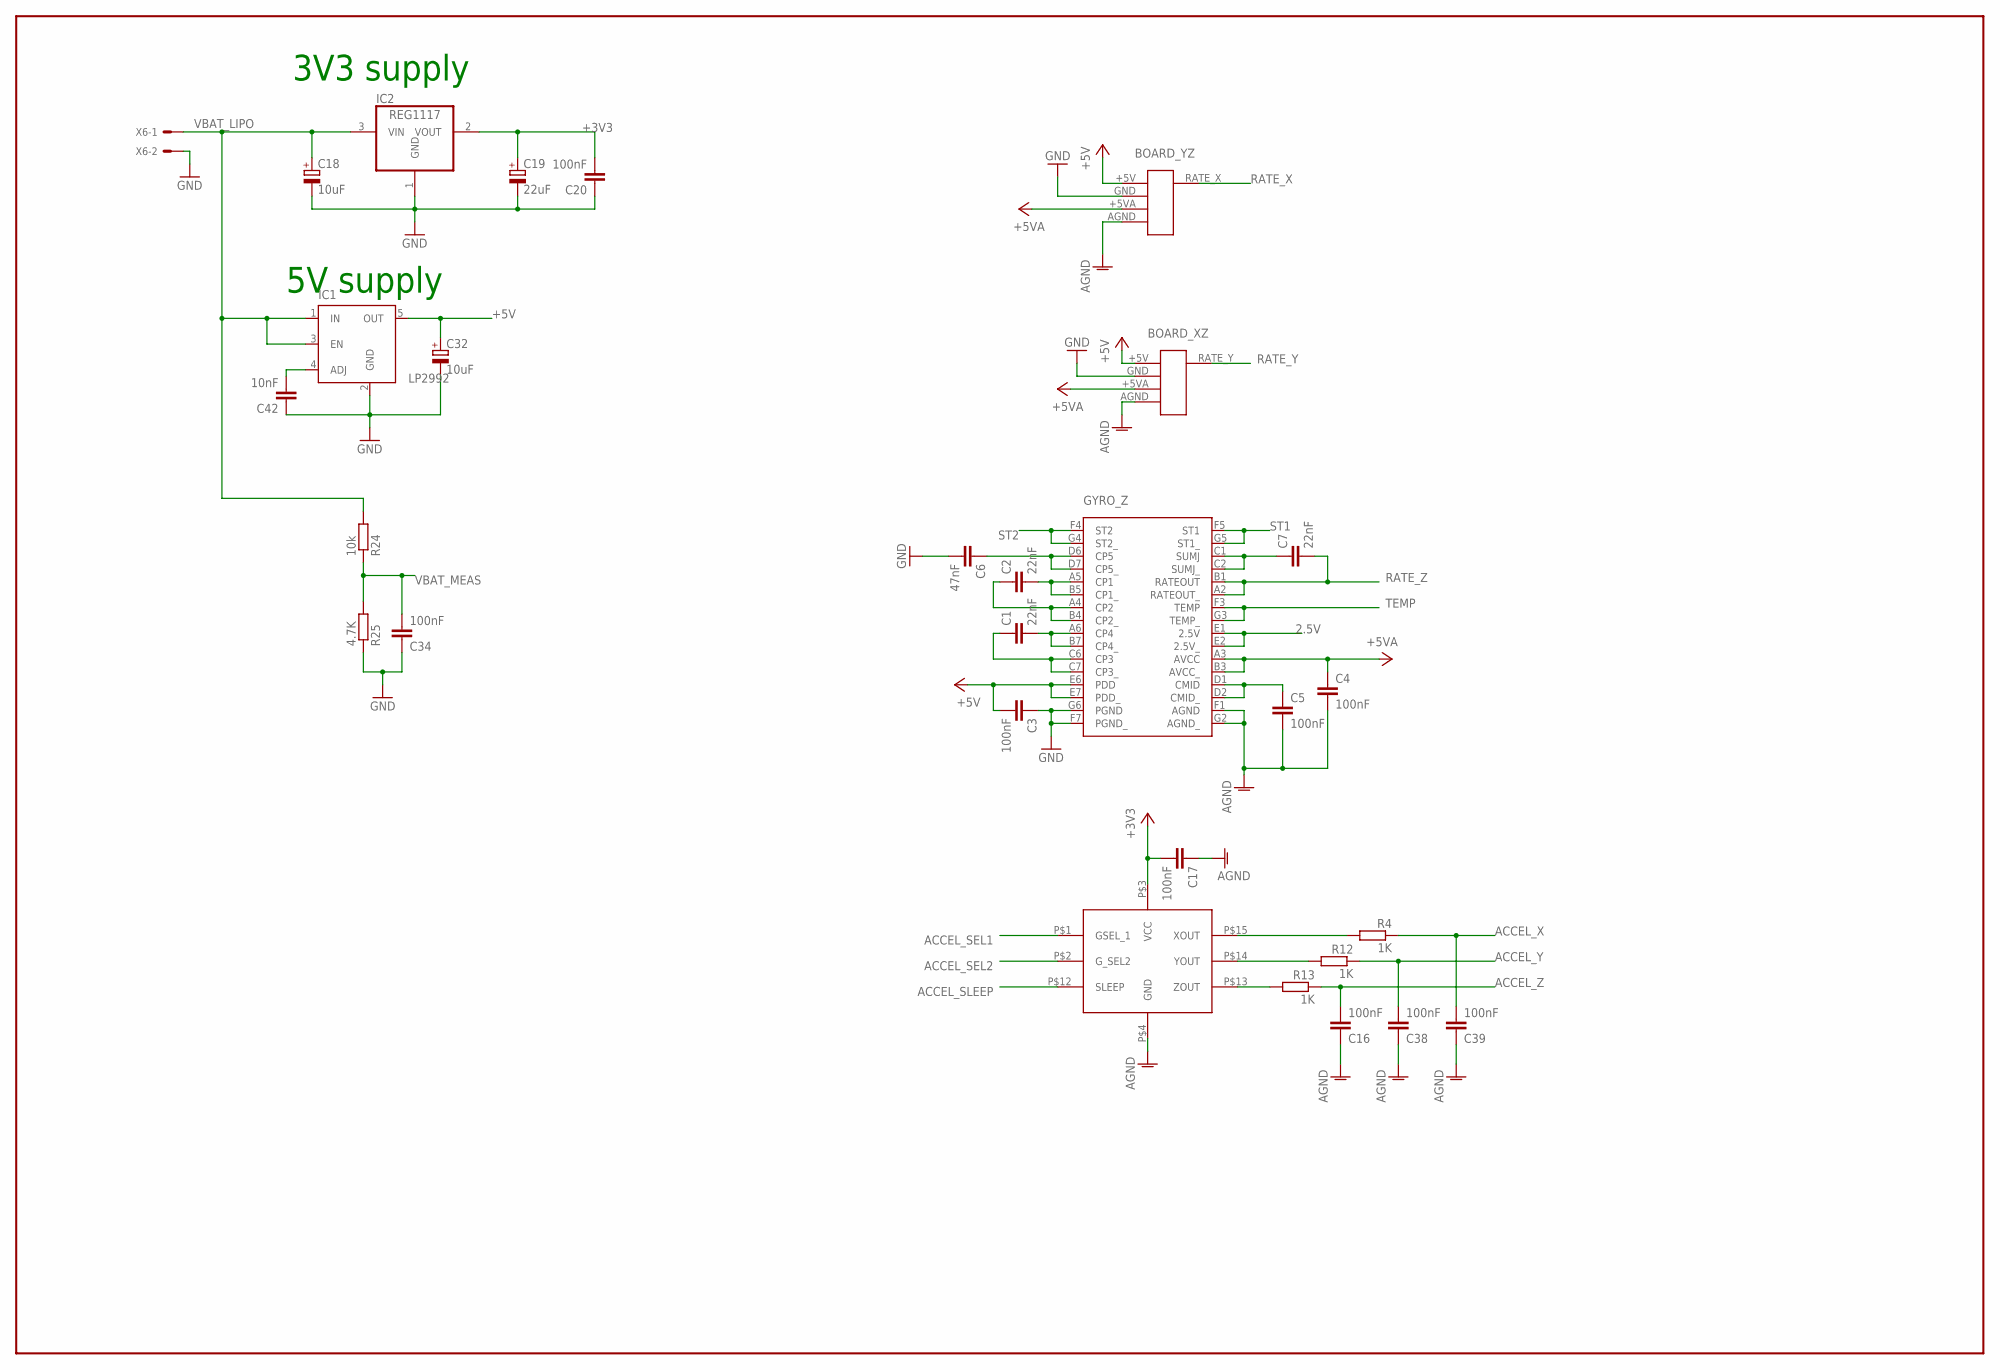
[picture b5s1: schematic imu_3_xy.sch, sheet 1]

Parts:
BOARD_XZ: IMU_XZ_3
BOARD_YZ: IMU_YZ_3
C1, C2, C7: 22nF; C0402K
C3, C4, C5, C16, C17, C34, C38, C39: 100nF; C0402K
C6: 47nF; C0402K
C18, C32: 10uF; A/3216-18R
C19: 22uF; B/3528-21R
C20: 100nF; C0603K
C42: 10nF; C0402K
GYRO_Z: ADXR; BC-32
IC1: LP2992; SOT23-5
IC2: REG1117; SOT223
R4, R12, R13: 1K; R0402
R24: 10k; R0402
R25: 4.7K; R0402
U$5: MMA7260; CASE162201
X6: 53048-02

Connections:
2.5V: GYRO_Z.E1 (2.5V), GYRO_Z.E2 (2.5V_)
+3V3: C17.2, C19.+, C20.2, IC2.2 (VOUT), U$5.P$3 (VCC); also elsewhere on the board
+5V: BOARD_XZ.+5V, BOARD_YZ.+5V, C3.2, C32.+, GYRO_Z.E6 (PDD), GYRO_Z.E7 (PDD_), IC1.5 (OUT); also elsewhere on the board
+5VA: BOARD_XZ.+5VA, BOARD_YZ.+5VA, C4.1, GYRO_Z.A3 (AVCC), GYRO_Z.B3 (AVCC_); also elsewhere on the board
ACCEL_SEL1: U$5.P$1 (GSEL_1); also elsewhere on the board
ACCEL_SEL2: U$5.P$2 (G_SEL2); also elsewhere on the board
ACCEL_SLEEP: U$5.P$12 (SLEEP); also elsewhere on the board
ACCEL_X: C39.2, R4.1; also elsewhere on the board
ACCEL_Y: C38.2, R12.1; also elsewhere on the board
ACCEL_Z: C16.2, R13.1; also elsewhere on the board
AGND: BOARD_XZ.AGND, BOARD_YZ.AGND, C4.2, C5.2, C16.1, C17.1, C38.1, C39.1, GYRO_Z.F1 (AGND), GYRO_Z.G2 (AGND_), U$5.P$4 (GND); also elsewhere on the board
GND: BOARD_XZ.GND, BOARD_YZ.GND, C3.1, C6.2, C18.-, C19.-, C20.1, C32.-, C34.1, C42.1, GYRO_Z.F7 (PGND_), GYRO_Z.G6 (PGND), IC1.2 (GND), IC2.1 (GND), R25.1, X6.2; also elsewhere on the board
unnamed: C1.2, GYRO_Z.A6 (CP4), GYRO_Z.B7 (CP4_)
unnamed: C1.1, GYRO_Z.C6 (CP3), GYRO_Z.C7 (CP3_)
unnamed: C2.2, GYRO_Z.A5 (CP1), GYRO_Z.B5 (CP1_)
unnamed: C2.1, GYRO_Z.A4 (CP2), GYRO_Z.B4 (CP2_)
unnamed: R4.2, U$5.P$15 (XOUT)
unnamed: C7.1, GYRO_Z.C1 (SUMJ), GYRO_Z.C2 (SUMJ_)
unnamed: C6.1, GYRO_Z.D6 (CP5), GYRO_Z.D7 (CP5_)
unnamed: C5.1, GYRO_Z.D1 (CMID), GYRO_Z.D2 (CMID_)
unnamed: R12.2, U$5.P$14 (YOUT)
unnamed: R13.2, U$5.P$13 (ZOUT)
unnamed: C42.2, IC1.4 (ADJ)
RATE_X: BOARD_YZ.RATE_X (RATE); also elsewhere on the board
RATE_Y: BOARD_XZ.RATE_Y (RATE); also elsewhere on the board
RATE_Z: C7.2, GYRO_Z.A2 (RATEOUT_), GYRO_Z.B1 (RATEOUT); also elsewhere on the board
ST1: GYRO_Z.F5 (ST1), GYRO_Z.G5 (ST1_)
ST2: GYRO_Z.F4 (ST2), GYRO_Z.G4 (ST2_)
TEMP: GYRO_Z.F3 (TEMP), GYRO_Z.G3 (TEMP_); also elsewhere on the board
VBAT_LIPO: C18.+, IC1.1 (IN), IC1.3 (EN), IC2.3 (VIN), R24.2, X6.1
VBAT_MEAS: C34.2, R24.1, R25.2; also elsewhere on the board

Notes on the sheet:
3V3 supply
5V supply

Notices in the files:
sensors/imu/aspirin/v2.1/aspirin-teardrops.brd:
Licensed under:
(C) 2010-2011 Antoine Drouin
(C) 2010-2012 Piotr Esden-Tempski
(C) 2011 Richard Hatano
(C) 2011 Joby Robotics
(C) 2011-2012 Transition Robotics
